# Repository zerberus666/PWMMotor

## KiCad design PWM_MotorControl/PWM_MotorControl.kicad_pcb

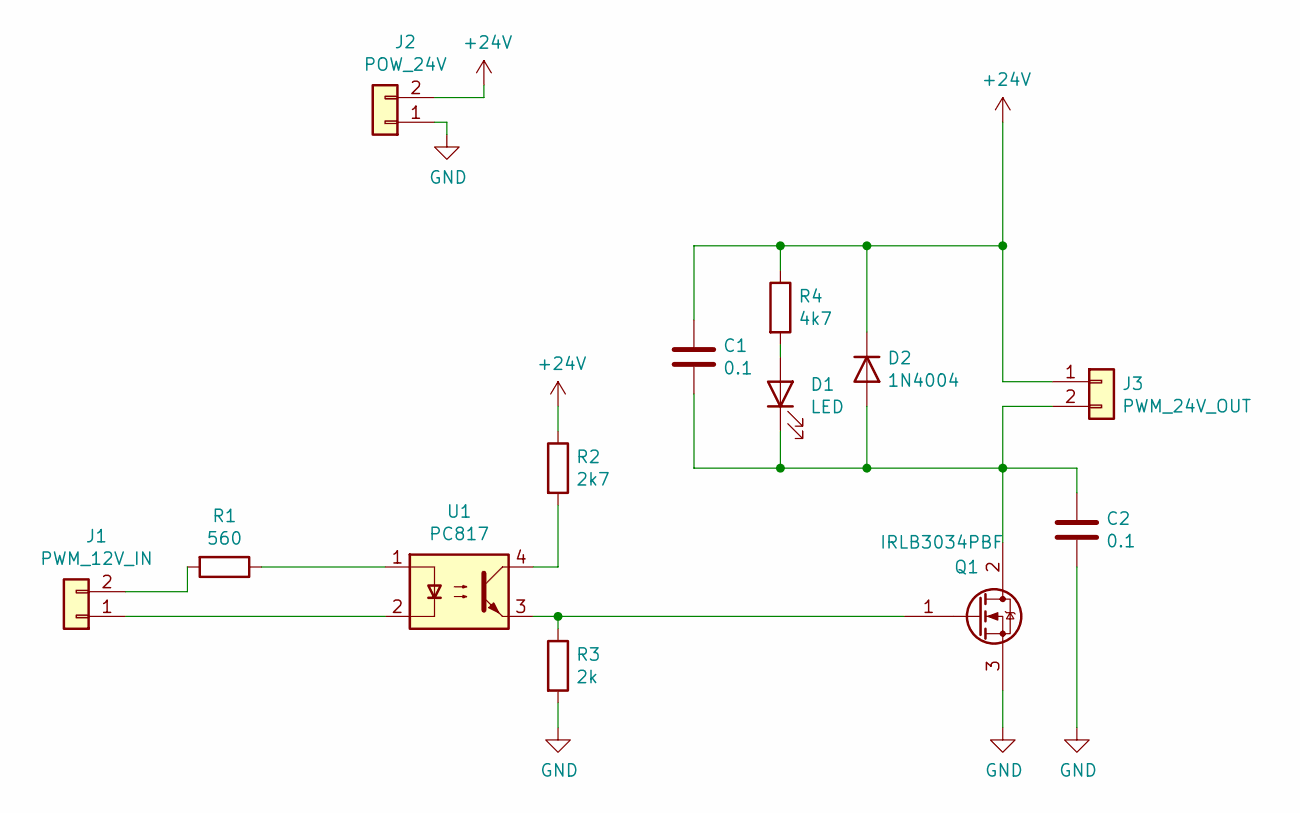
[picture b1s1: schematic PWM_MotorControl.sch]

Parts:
C1, C2: 0.1; C_Disc_D4.7mm_W2.5mm_P5.00mm
D1: LED; LED_D5.0mm
D2: 1N4004; D_DO-41_SOD81_P10.16mm_Horizontal
J1: PWM_12V_IN; DG142V-5.08-2
J2: POW_24V; DG142V-5.08-2
J3: PWM_24V_OUT; DG142V-5.08-2
Q1: IRLB3034PBF; TO254P483X1016X1501-3P; Manufacturer_Part_Number IRLB3034PBF; Mouser Part Number 942-IRLB3034PBF
R1: 560; R_Axial_DIN0204_L3.6mm_D1.6mm_P7.62mm_Horizontal
R2: 2k7; R_Axial_DIN0204_L3.6mm_D1.6mm_P7.62mm_Horizontal
R3: 2k; R_Axial_DIN0204_L3.6mm_D1.6mm_P7.62mm_Horizontal
R4: 4k7; R_Axial_DIN0204_L3.6mm_D1.6mm_P7.62mm_Horizontal
U1: PC817; DIP-4_W7.62mm

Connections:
+24V: C1.1, D2.1 (K), J2.2, J3.1, R2.1, R4.1
GND: C2.2, J2.1, Q1.3, R3.2
unnamed: C1.2, C2.1, D1.1 (K), D2.2 (A), J3.2, Q1.2
unnamed: D1.2 (A), R4.2
unnamed: J1.1, U1.2
unnamed: J1.2, R1.2
unnamed: Q1.1, R3.1, U1.3
unnamed: R1.1, U1.1
unnamed: R2.2, U1.4

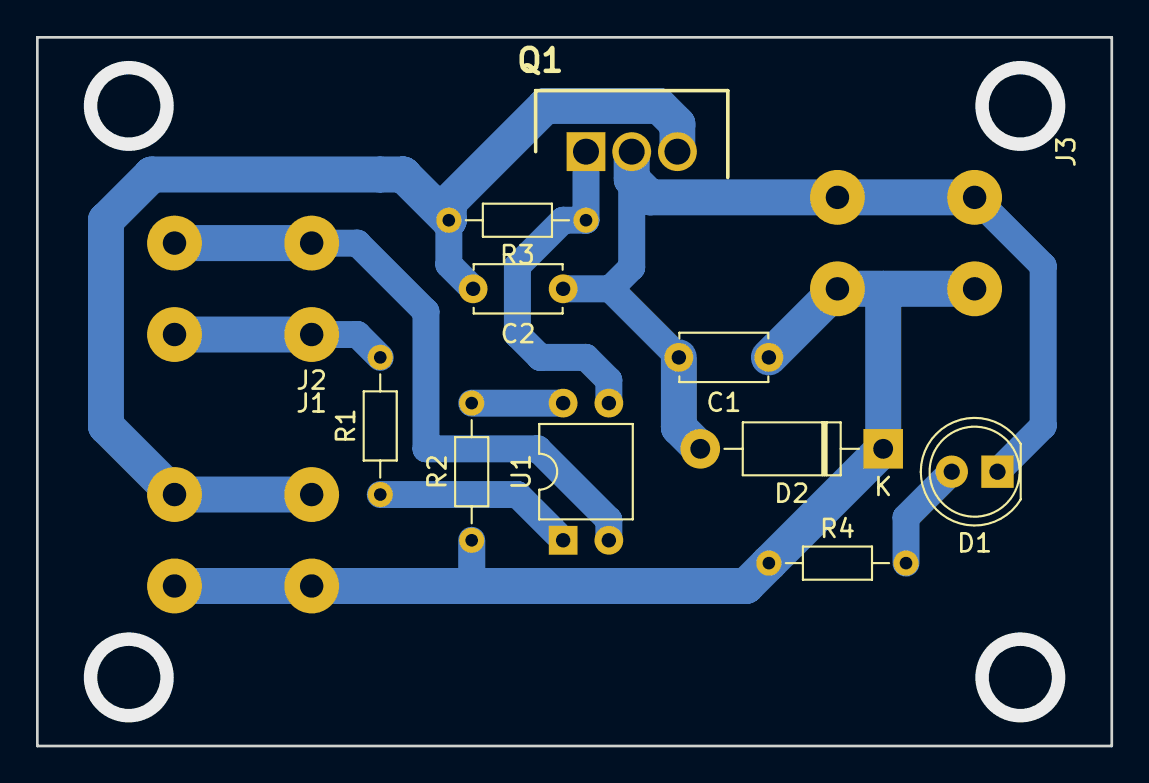
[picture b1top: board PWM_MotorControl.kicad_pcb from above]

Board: 2 copper layers, 59.7 x 39.4 mm, 13 parts (0 on the bottom side), 9 nets.

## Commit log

2021-11-10 initial
